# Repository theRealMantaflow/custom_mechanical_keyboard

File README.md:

# Custom STM32 Mechanical Keyboard

This repository contains the hardware design files (PCB schematics and mechanical enclosures) for a custom mechanical keyboard. The PCB is designed in **KiCad**, and the case/mechanical components are modeled in **FreeCAD**.

## Features

* **Microcontroller:** STM32F405RGT
* **Connectivity:** USB-C 2.0 with dedicated ESD protection (USBLC6-2SC6)
* **Switch Matrix:** 6x16 layout supporting up to 96 keys
* **Switches:** Cherry MX compatible, utilizing Khail hot-swap sockets
* **Anti-Ghosting:** Per-key diodes for full N-Key Rollover (NKRO)
* **Extras:** Support for a rotary encoder and broken-out SWD/I2C pins for easy debugging and expansion

## Repository Structure

* `/` - Contains the KiCad project, schematics, and PCB layout files.
* `/case/` - Contains the FreeCAD design files for the keyboard case and plate.
* `/pcbway_production/` - Contains the gerber files.

## Prerequisites & Environment Setup

Before opening the KiCad project files, you need to configure your KiCad environment with the appropriate custom libraries and plugins used in this design. 

### KiCad Package Installation

Follow these steps exactly to ensure all footprints and symbols load correctly:

1. **Add the ebastler repository:**
   * Open KiCad and go to the **Plugin and Content Manager**.
   * Click on **Manage Repositories** (usually at the bottom left).
   * Add a new repository with the following URL:
     [https://raw.githubusercontent.com/ebastler/KiCad-repository/main/repository.json](https://raw.githubusercontent.com/ebastler/KiCad-repository/main/repository.json)
2. **Install custom libraries:**
   * Switch the repository dropdown at the top of the Plugin Manager to the newly added `ebastler` repo.
   * Find and install the **`marbastlib`** package.
3. **Switch back to the official repository:**
   * Change the repository dropdown back to the official **KiCad** repository.
4. **Install required keyboard packages:**
   * Search for and install the **`Keyswitch KiCad Library`**.
   * *(Optional)* If you plan on modifying the PCB layout, install the **`Keyboard footprints placer`** plugin to make routing and placing switches easier.

Once these packages are installed, you can safely open the `.kicad_pro` file.

## Contributions

Feel free to fork this repository and submit pull requests if you have improvements for the PCB routing or case design. 

My Ko-fi link if you wanna support my efforts:  [Kofi](https://ko-fi.com/mantaflow)

## Thanks

Inspired from: [Modern Hobbyist](https://www.youtube.com/watch?v=u13yRbBiRYM)

## License
This project is licensed under the **GNU General Public License v3.0 (GPL-3.0)**. See the [LICENSE](LICENSE.txt) file for more details.

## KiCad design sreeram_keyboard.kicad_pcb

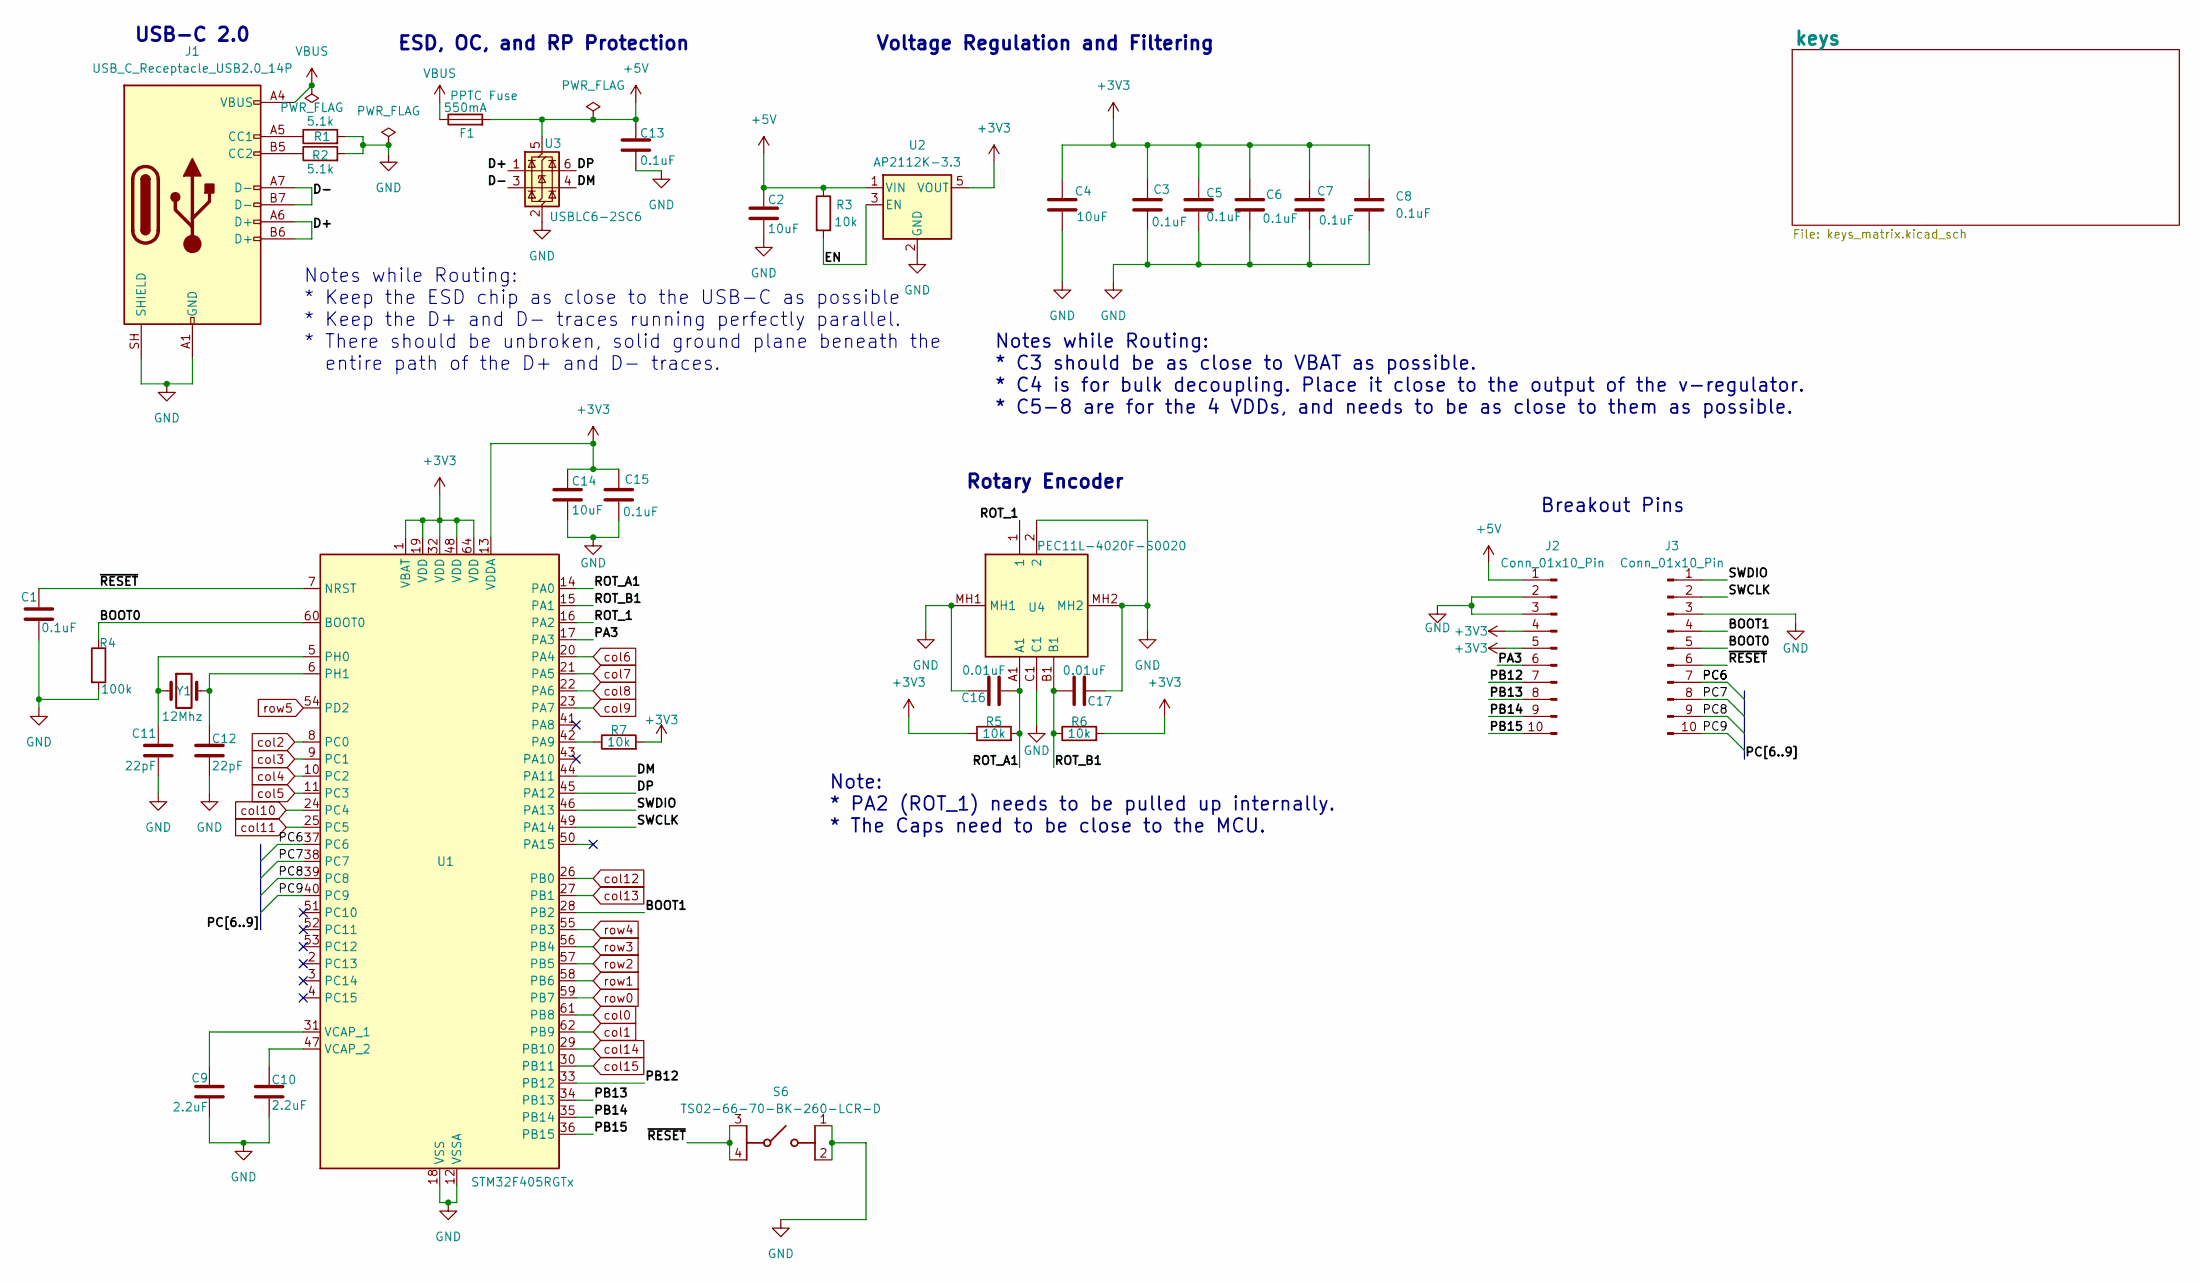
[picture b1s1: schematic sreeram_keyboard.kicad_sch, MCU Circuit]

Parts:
C1, C3, C5, C6, C7, C8, C13, C15: 0.1uF; C_0805_2012Metric_Pad1.18x1.45mm_HandSolder
C2, C4, C14: 10uF; C_0805_2012Metric_Pad1.18x1.45mm_HandSolder
C9, C10: 2.2uF; C_0805_2012Metric_Pad1.18x1.45mm_HandSolder
C11, C12: 22pF; C_0805_2012Metric_Pad1.18x1.45mm_HandSolder
C16, C17: 0.01uF; C_0805_2012Metric_Pad1.18x1.45mm_HandSolder
F1: 550mA; Fuse_1206_3216Metric_Pad1.42x1.75mm_HandSolder
J1: USB_C_Receptacle_USB2.0_14P; USB_C_Receptacle_GCT_USB4085
J2, J3: Conn_01x10_Pin; PinHeader_1x10_P2.54mm_Vertical
R1, R2: 5.1k; R_0805_2012Metric_Pad1.20x1.40mm_HandSolder
R3, R5, R6, R7: 10k; R_0805_2012Metric_Pad1.20x1.40mm_HandSolder
R4: 100k; R_0805_2012Metric_Pad1.20x1.40mm_HandSolder
S6: TS02-66-70-BK-260-LCR-D; TS0266100BK100LCRD; Mouser Part Number 179-TS026670BK260LCR
U1: STM32F405RGTx; LQFP-64_10x10mm_P0.5mm
U2: AP2112K-3.3; SOT95P285X140-5N
U3: USBLC6-2SC6; SOT-23-6
U4: PEC11L-4020F-S0020; PEC11L4120FS0020; Mouser Part Number 652-PEC11L4020FS0020
Y1: 12Mhz; ABLS

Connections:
+3V3: C3.1, C4.1, C5.1, C6.1, C7.1, C8.1, C14.1, C15.1, J2.4, J2.5, R5.1, R6.2, R7.2, U1.1 (VBAT), U1.13 (VDDA), U1.19 (VDD), U1.32 (VDD), U1.48 (VDD), U1.64 (VDD), U2.5 (VOUT)
+5V: C2.1, C13.1, F1.2, J2.1, R3.1, U2.1 (VIN), U3.5 (VBUS)
/BOOT0: J3.5, R4.1, U1.60 (BOOT0)
/BOOT1: J3.4, U1.28 (PB2)
/D+: J1.A6 (D+), J1.B6 (D+), U3.1 (I/O1)
/D-: J1.A7 (D-), J1.B7 (D-), U3.3 (I/O2)
/DM: U1.44 (PA11), U3.4 (I/O2)
/DP: U1.45 (PA12), U3.6 (I/O1)
/EN: R3.2, U2.3 (EN)
/PA3: J2.6, U1.17 (PA3)
/PB12: J2.7, U1.33 (PB12)
/PB13: J2.8, U1.34 (PB13)
/PB14: J2.9, U1.35 (PB14)
/PB15: J2.10, U1.36 (PB15)
/PC6: J3.7, U1.37 (PC6)
/PC7: J3.8, U1.38 (PC7)
/PC8: J3.9, U1.39 (PC8)
/PC9: J3.10, U1.40 (PC9)
/ROT_1: U1.16 (PA2), U4.1
/ROT_A1: C16.2, R5.2, U1.14 (PA0), U4.A1
/ROT_B1: C17.1, R6.1, U1.15 (PA1), U4.B1
/SWCLK: J3.2, U1.49 (PA14)
/SWDIO: J3.1, U1.46 (PA13)
/~RESET: C1.1, J3.6, S6.3 (COM_1), S6.4 (COM_2), U1.7 (NRST)
GND: C1.2, C2.2, C3.2, C4.2, C5.2, C6.2, C7.2, C8.2, C9.2, C10.2, C11.2, C12.2, C13.2, C14.2, C15.2, C16.1, C17.2, J1.A1 (GND), J1.A12 (GND), J1.B1 (GND), J1.B12 (GND), J1.SH (SHIELD), J2.2, J2.3, J3.3, R1.2, R2.2, R4.2, S6.1 (NO_1), S6.2 (NO_2), U1.12 (VSSA), U1.18 (VSS), U1.63 (VSS), U2.2 (GND), U3.2 (GND), U4.2, U4.C1, U4.MH1, U4.MH2
unnamed: J1.A5 (CC1), R1.1
unnamed: J1.B5 (CC2), R2.1
unnamed: R7.1, U1.42 (PA9)
unnamed: C11.1, U1.5 (PH0), Y1.1
unnamed: C12.1, U1.6 (PH1), Y1.2
unnamed: C9.1, U1.31 (VCAP_1)
unnamed: C10.1, U1.47 (VCAP_2)
VBUS: F1.1, J1.A4 (VBUS), J1.A9 (VBUS), J1.B4 (VBUS), J1.B9 (VBUS)
col0: U1.61 (PB8); also elsewhere on the board
col1: U1.62 (PB9); also elsewhere on the board
col2: U1.8 (PC0); also elsewhere on the board
col3: U1.9 (PC1); also elsewhere on the board
col4: U1.10 (PC2); also elsewhere on the board
col5: U1.11 (PC3); also elsewhere on the board
col6: U1.20 (PA4); also elsewhere on the board
col7: U1.21 (PA5); also elsewhere on the board
col8: U1.22 (PA6); also elsewhere on the board
col9: U1.23 (PA7); also elsewhere on the board
col10: U1.24 (PC4); also elsewhere on the board
col11: U1.25 (PC5); also elsewhere on the board
col12: U1.26 (PB0); also elsewhere on the board
col13: U1.27 (PB1); also elsewhere on the board
col14: U1.29 (PB10); also elsewhere on the board
col15: U1.30 (PB11); also elsewhere on the board
row0: U1.59 (PB7); also elsewhere on the board
row1: U1.58 (PB6); also elsewhere on the board
row2: U1.57 (PB5); also elsewhere on the board
row3: U1.56 (PB4); also elsewhere on the board
row4: U1.55 (PB3); also elsewhere on the board
row5: U1.54 (PD2); also elsewhere on the board

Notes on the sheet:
Notes while Routing: * C3 should be as close to VBAT as possible. * C4 is for bulk decoupling. Place it close to the output of the v-regulator. * C5-8 are for the 4 VDDs, and needs to be as close to them as possible.
Notes while Routing: * Keep the ESD chip as close to the USB-C as possible * Keep the D+ and D- traces running perfectly parallel. * There should be unbroken, solid ground plane beneath the entire path of the D+ and D- traces.
USB-C 2.0
Voltage Regulation and Filtering
ESD, OC, and RP Protection
Note: * PA2 (ROT_1) needs to be pulled up internally. * The Caps need to be close to the MCU.
Rotary Encoder
Breakout Pins

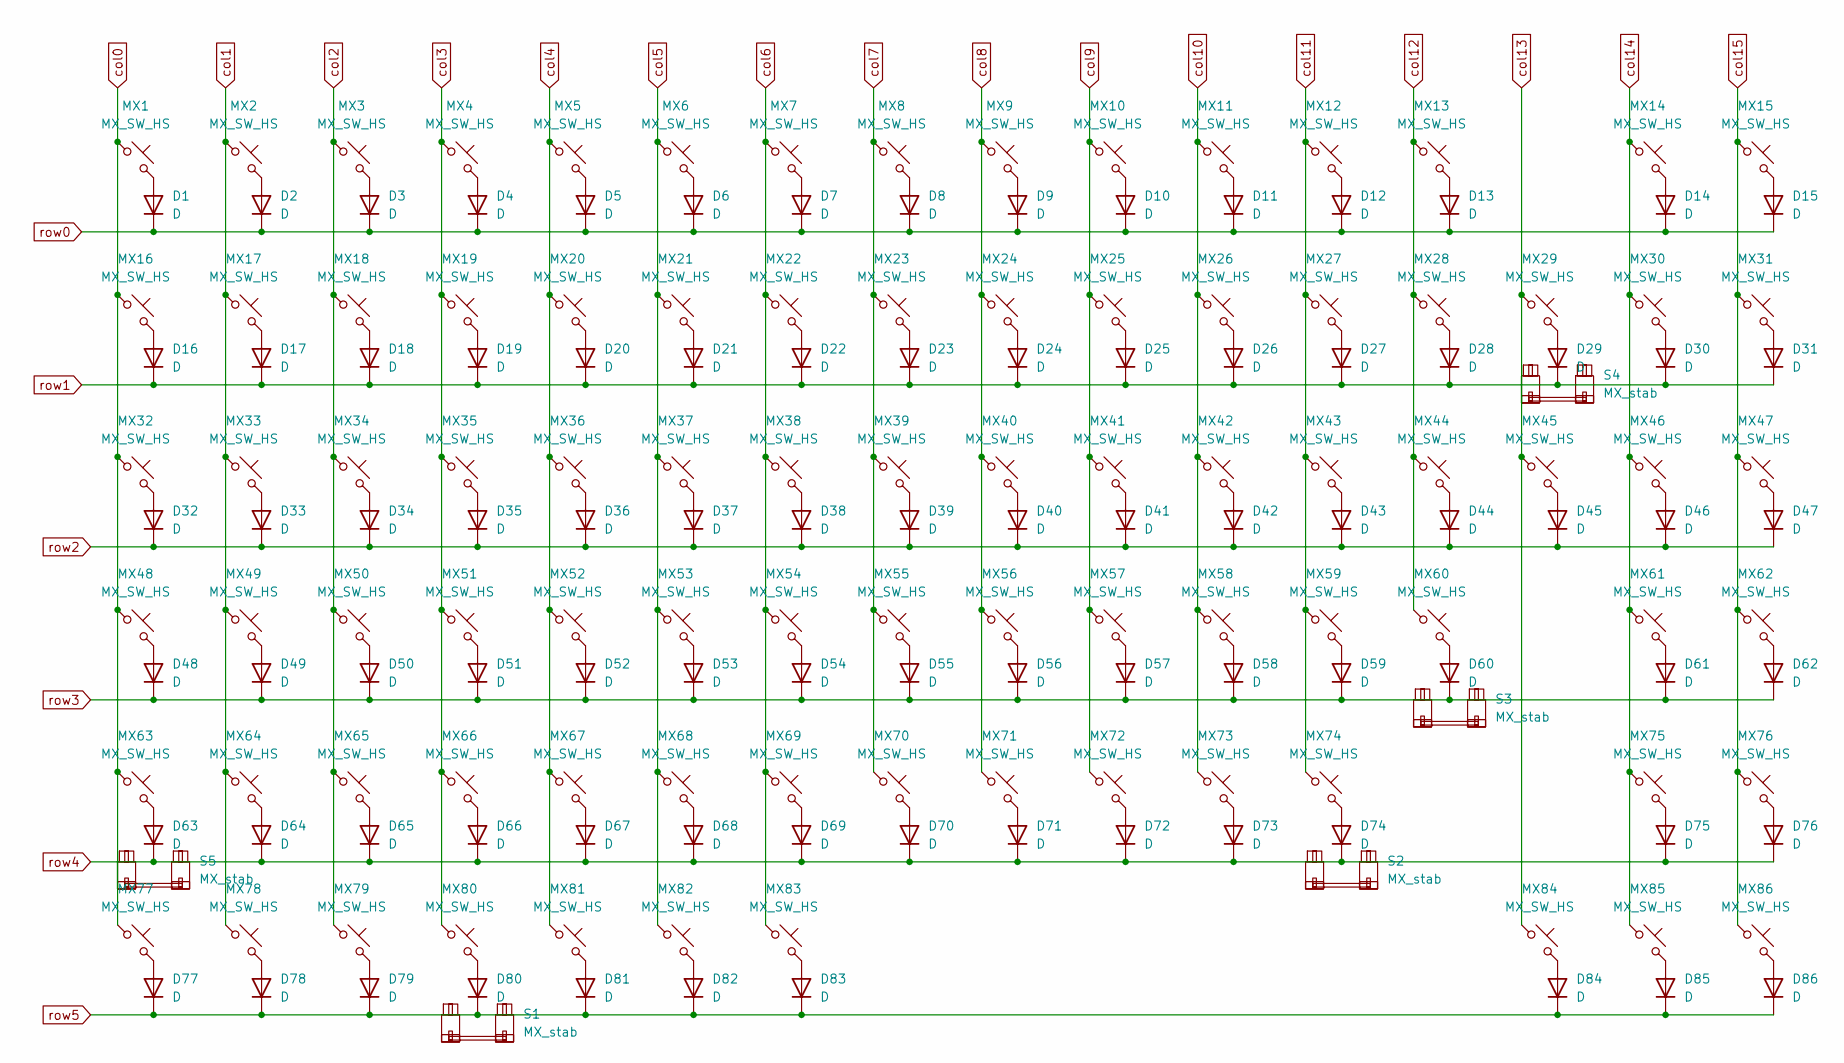
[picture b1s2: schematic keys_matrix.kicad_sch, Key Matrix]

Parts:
D1, D2, D3, D4, D5, D6, D7, D8, D9, D10, D11, D12, D13, D14, D15, D16, D17, D18, D19, D20, D21, D22, D23, D24, D25, D26, D27, D28, D29, D30, D31, D32, D33, D34, D35, D36, D37, D38, D39, D40, D41, D42, D43, D44, D45, D46, D47, D48, D49, D50, D51, D52, D53, D54, D55, D56, D57, D58, D59, D60, D61, D62, D63, D64, D65, D66, D67, D68, D69, D70, D71, D72, D73, D74, D75, D76, D77, D78, D79, D80, D81, D82, D83, D84, D85, D86: D; D_SOD-123
MX1, MX2, MX3, MX4, MX5, MX6, MX7, MX8, MX9, MX10, MX11, MX12, MX13, MX14, MX15, MX16, MX17, MX18, MX19, MX20, MX21, MX22, MX23, MX24, MX25, MX26, MX27, MX28, MX29, MX30, MX31, MX32, MX33, MX34, MX35, MX36, MX37, MX38, MX39, MX40, MX41, MX42, MX43, MX44, MX45, MX46, MX47, MX48, MX49, MX50, MX51, MX52, MX53, MX54, MX55, MX56, MX57, MX58, MX59, MX60, MX61, MX62, MX63, MX64, MX65, MX66, MX67, MX68, MX69, MX70, MX71, MX72, MX73, MX74, MX75, MX76, MX77, MX78, MX79, MX80, MX81, MX82, MX83, MX84, MX85, MX86: MX_SW_HS; SW_MX_HS_S_CPG151101S11_1u
S1: MX_stab; STAB_MX_P_6.25u
S2, S3, S4, S5: MX_stab; STAB_MX_P_2u

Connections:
unnamed: D1.2 (A), MX1.2
unnamed: D2.2 (A), MX2.2
unnamed: D3.2 (A), MX3.2
unnamed: D4.2 (A), MX4.2
unnamed: D5.2 (A), MX5.2
unnamed: D6.2 (A), MX6.2
unnamed: D7.2 (A), MX7.2
unnamed: D8.2 (A), MX8.2
unnamed: D9.2 (A), MX9.2
unnamed: D10.2 (A), MX10.2
unnamed: D11.2 (A), MX11.2
unnamed: D12.2 (A), MX12.2
unnamed: D13.2 (A), MX13.2
unnamed: D14.2 (A), MX14.2
unnamed: D15.2 (A), MX15.2
unnamed: D16.2 (A), MX16.2
unnamed: D17.2 (A), MX17.2
unnamed: D18.2 (A), MX18.2
unnamed: D19.2 (A), MX19.2
unnamed: D20.2 (A), MX20.2
unnamed: D21.2 (A), MX21.2
unnamed: D22.2 (A), MX22.2
unnamed: D23.2 (A), MX23.2
unnamed: D24.2 (A), MX24.2
unnamed: D25.2 (A), MX25.2
unnamed: D26.2 (A), MX26.2
unnamed: D27.2 (A), MX27.2
unnamed: D28.2 (A), MX28.2
unnamed: D29.2 (A), MX29.2
unnamed: D30.2 (A), MX30.2
unnamed: D31.2 (A), MX31.2
unnamed: D32.2 (A), MX32.2
unnamed: D33.2 (A), MX33.2
unnamed: D34.2 (A), MX34.2
unnamed: D35.2 (A), MX35.2
unnamed: D36.2 (A), MX36.2
unnamed: D37.2 (A), MX37.2
unnamed: D38.2 (A), MX38.2
unnamed: D39.2 (A), MX39.2
unnamed: D40.2 (A), MX40.2
unnamed: D41.2 (A), MX41.2
unnamed: D42.2 (A), MX42.2
unnamed: D43.2 (A), MX43.2
unnamed: D44.2 (A), MX44.2
unnamed: D45.2 (A), MX45.2
unnamed: D46.2 (A), MX46.2
unnamed: D47.2 (A), MX47.2
unnamed: D48.2 (A), MX48.2
unnamed: D49.2 (A), MX49.2
unnamed: D50.2 (A), MX50.2
unnamed: D51.2 (A), MX51.2
unnamed: D52.2 (A), MX52.2
unnamed: D53.2 (A), MX53.2
unnamed: D54.2 (A), MX54.2
unnamed: D55.2 (A), MX55.2
unnamed: D56.2 (A), MX56.2
unnamed: D57.2 (A), MX57.2
unnamed: D58.2 (A), MX58.2
unnamed: D59.2 (A), MX59.2
unnamed: D60.2 (A), MX60.2
unnamed: D61.2 (A), MX61.2
unnamed: D62.2 (A), MX62.2
unnamed: D63.2 (A), MX63.2
unnamed: D64.2 (A), MX64.2
unnamed: D65.2 (A), MX65.2
unnamed: D66.2 (A), MX66.2
unnamed: D67.2 (A), MX67.2
unnamed: D68.2 (A), MX68.2
unnamed: D69.2 (A), MX69.2
unnamed: D70.2 (A), MX70.2
unnamed: D71.2 (A), MX71.2
unnamed: D72.2 (A), MX72.2
unnamed: D73.2 (A), MX73.2
unnamed: D74.2 (A), MX74.2
unnamed: D75.2 (A), MX75.2
unnamed: D76.2 (A), MX76.2
unnamed: D77.2 (A), MX77.2
unnamed: D78.2 (A), MX78.2
unnamed: D79.2 (A), MX79.2
unnamed: D80.2 (A), MX80.2
unnamed: D81.2 (A), MX81.2
unnamed: D82.2 (A), MX82.2
unnamed: D83.2 (A), MX83.2
unnamed: D84.2 (A), MX84.2
unnamed: D85.2 (A), MX85.2
unnamed: D86.2 (A), MX86.2
col0: MX1.1, MX16.1, MX32.1, MX48.1, MX63.1, MX77.1; also elsewhere on the board
col1: MX2.1, MX17.1, MX33.1, MX49.1, MX64.1, MX78.1; also elsewhere on the board
col2: MX3.1, MX18.1, MX34.1, MX50.1, MX65.1, MX79.1; also elsewhere on the board
col3: MX4.1, MX19.1, MX35.1, MX51.1, MX66.1, MX80.1; also elsewhere on the board
col4: MX5.1, MX20.1, MX36.1, MX52.1, MX67.1, MX81.1; also elsewhere on the board
col5: MX6.1, MX21.1, MX37.1, MX53.1, MX68.1, MX82.1; also elsewhere on the board
col6: MX7.1, MX22.1, MX38.1, MX54.1, MX69.1, MX83.1; also elsewhere on the board
col7: MX8.1, MX23.1, MX39.1, MX55.1, MX70.1; also elsewhere on the board
col8: MX9.1, MX24.1, MX40.1, MX56.1, MX71.1; also elsewhere on the board
col9: MX10.1, MX25.1, MX41.1, MX57.1, MX72.1; also elsewhere on the board
col10: MX11.1, MX26.1, MX42.1, MX58.1, MX73.1; also elsewhere on the board
col11: MX12.1, MX27.1, MX43.1, MX59.1, MX74.1; also elsewhere on the board
col12: MX13.1, MX28.1, MX44.1, MX60.1; also elsewhere on the board
col13: MX29.1, MX45.1, MX84.1; also elsewhere on the board
col14: MX14.1, MX30.1, MX46.1, MX61.1, MX75.1, MX85.1; also elsewhere on the board
col15: MX15.1, MX31.1, MX47.1, MX62.1, MX76.1, MX86.1; also elsewhere on the board
row0: D1.1 (K), D2.1 (K), D3.1 (K), D4.1 (K), D5.1 (K), D6.1 (K), D7.1 (K), D8.1 (K), D9.1 (K), D10.1 (K), D11.1 (K), D12.1 (K), D13.1 (K), D14.1 (K), D15.1 (K); also elsewhere on the board
row1: D16.1 (K), D17.1 (K), D18.1 (K), D19.1 (K), D20.1 (K), D21.1 (K), D22.1 (K), D23.1 (K), D24.1 (K), D25.1 (K), D26.1 (K), D27.1 (K), D28.1 (K), D29.1 (K), D30.1 (K), D31.1 (K); also elsewhere on the board
row2: D32.1 (K), D33.1 (K), D34.1 (K), D35.1 (K), D36.1 (K), D37.1 (K), D38.1 (K), D39.1 (K), D40.1 (K), D41.1 (K), D42.1 (K), D43.1 (K), D44.1 (K), D45.1 (K), D46.1 (K), D47.1 (K); also elsewhere on the board
row3: D48.1 (K), D49.1 (K), D50.1 (K), D51.1 (K), D52.1 (K), D53.1 (K), D54.1 (K), D55.1 (K), D56.1 (K), D57.1 (K), D58.1 (K), D59.1 (K), D60.1 (K), D61.1 (K), D62.1 (K); also elsewhere on the board
row4: D63.1 (K), D64.1 (K), D65.1 (K), D66.1 (K), D67.1 (K), D68.1 (K), D69.1 (K), D70.1 (K), D71.1 (K), D72.1 (K), D73.1 (K), D74.1 (K), D75.1 (K), D76.1 (K); also elsewhere on the board
row5: D77.1 (K), D78.1 (K), D79.1 (K), D80.1 (K), D81.1 (K), D82.1 (K), D83.1 (K), D84.1 (K), D85.1 (K), D86.1 (K); also elsewhere on the board

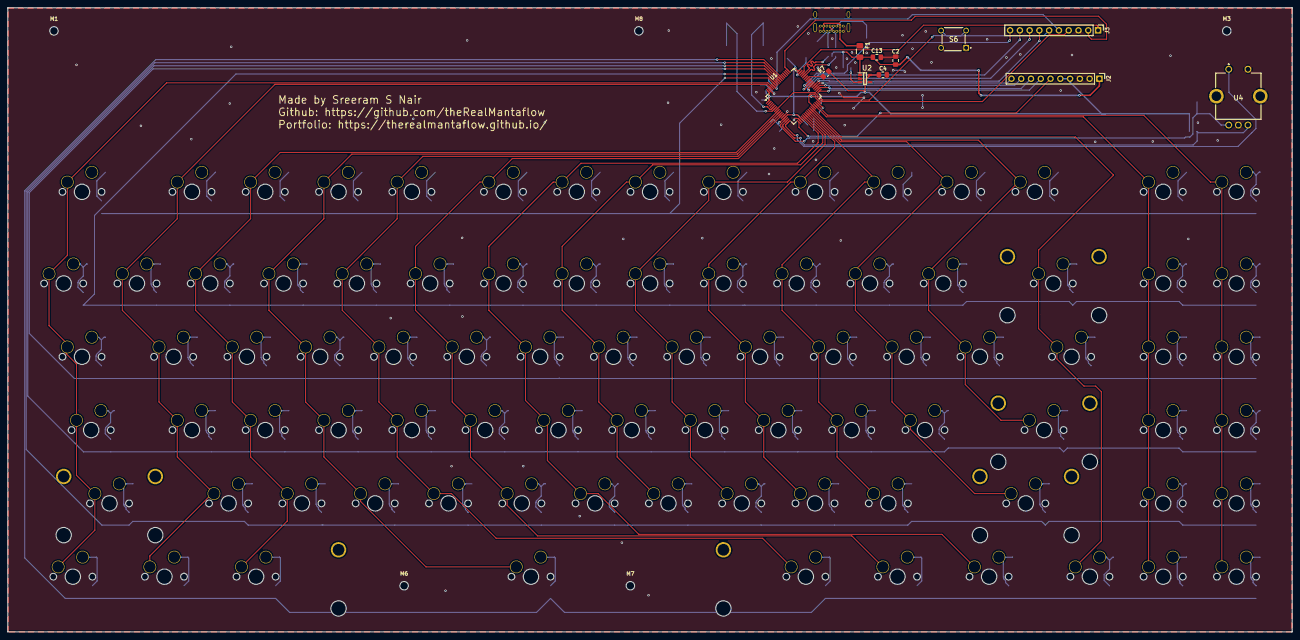
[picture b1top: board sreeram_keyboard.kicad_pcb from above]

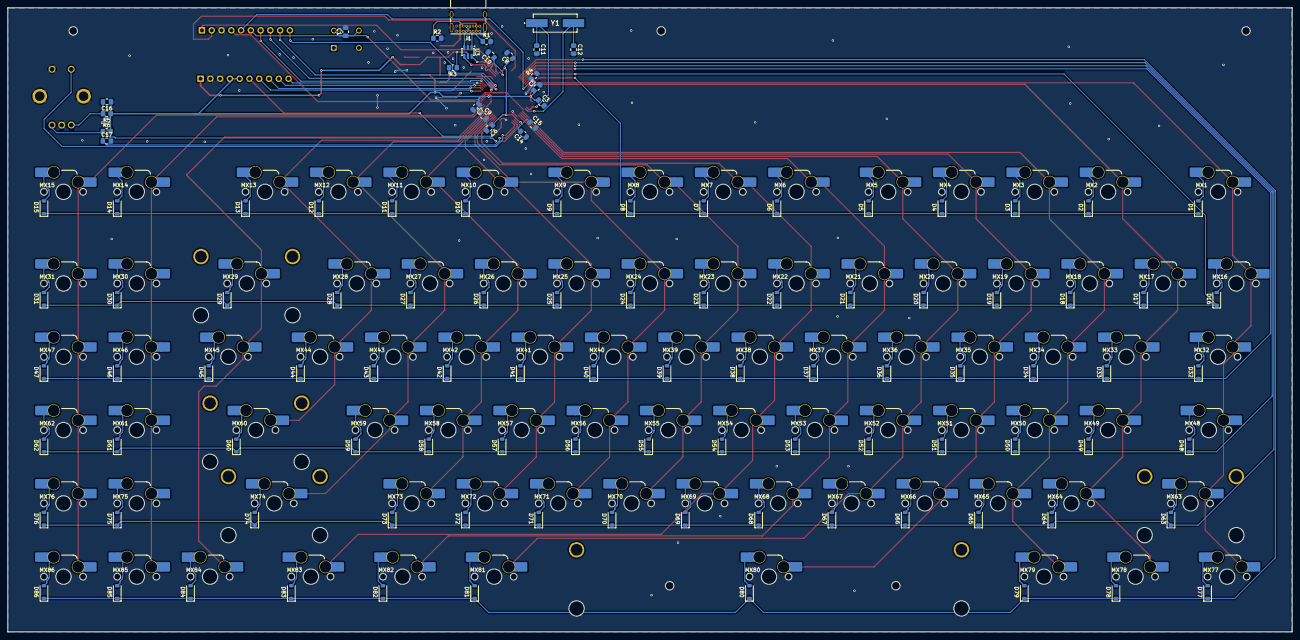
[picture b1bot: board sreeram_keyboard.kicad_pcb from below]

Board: 2 copper layers, 333.8 x 162.2 mm, 216 parts (195 on the bottom side), 141 nets.

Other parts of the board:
M1, M3, M6, M7, M8: MountingHole_2.2mm_M2

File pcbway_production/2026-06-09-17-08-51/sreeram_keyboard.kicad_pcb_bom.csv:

Designator,Quantity,Value,Footprint,Package,MPN,DNP,Mount_Type,KiLib_Generator
"C1, C13, C15, C3, C5, C6, C7, C8",8,0.1uF,C_0805_2012Metric_Pad1.18x1.45mm_HandSolder,,,,smt,SMD_2terminal_chip_molded
"C10, C9",2,2.2uF,C_0805_2012Metric_Pad1.18x1.45mm_HandSolder,,,,smt,SMD_2terminal_chip_molded
"C11, C12",2,22pF,C_0805_2012Metric_Pad1.18x1.45mm_HandSolder,,,,smt,SMD_2terminal_chip_molded
"C14, C2, C4",3,10uF,C_0805_2012Metric_Pad1.18x1.45mm_HandSolder,,,,smt,SMD_2terminal_chip_molded
"C16, C17",2,0.01uF,C_0805_2012Metric_Pad1.18x1.45mm_HandSolder,,,,smt,SMD_2terminal_chip_molded
"D1, D10, D11, D12, D13, D14, D15, D16, D17, D18, D19, D2, D20, D21, D22, D23, D24, D25, D26, D27, D28, D29, D3, D30, D31, D32, D33, D34, D35, D36, D37, D38, D39, D4, D40, D41, D42, D43, D44, D45, D46, D47, D48, D49, D5, D50, D51, D52, D53, D54, D55, D56, D57, D58, D59, D6, D60, D61, D62, D63, D64, D65, D66, D67, D68, D69, D7, D70, D71, D72, D73, D74, D75, D76, D77, D78, D79, D8, D80, D81, D82, D83, D84, D85, D86, D9",86,D,D_SOD-123,,,,smt,
F1,1,550mA,Fuse_1206_3216Metric_Pad1.42x1.75mm_HandSolder,,,,smt,SMD_2terminal_chip_molded
J1,1,USB_C_Receptacle_USB2.0_14P,USB_C_Receptacle_GCT_USB4085,,,,tht,
"J2, J3",2,Conn_01x10_Pin,PinHeader_1x10_P2.54mm_Vertical,,,,tht,connector/pin_header_socket
"MX1, MX10, MX11, MX12, MX13, MX14, MX15, MX16, MX17, MX18, MX19, MX2, MX20, MX21, MX22, MX23, MX24, MX25, MX26, MX27, MX28, MX29, MX3, MX30, MX31, MX32, MX33, MX34, MX35, MX36, MX37, MX38, MX39, MX4, MX40, MX41, MX42, MX43, MX44, MX45, MX46, MX47, MX48, MX49, MX5, MX50, MX51, MX52, MX53, MX54, MX55, MX56, MX57, MX58, MX59, MX6, MX60, MX61, MX62, MX63, MX64, MX65, MX66, MX67, MX68, MX69, MX7, MX70, MX71, MX72, MX73, MX74, MX75, MX76, MX77, MX78, MX79, MX8, MX80, MX81, MX82, MX83, MX84, MX85, MX86, MX9",86,MX_SW_HS,SW_MX_HS_S_CPG151101S11_1u,,,,smt,
"R1, R2",2,5.1k,R_0805_2012Metric_Pad1.20x1.40mm_HandSolder,,,,smt,SMD_2terminal_chip_molded
"R3, R5, R6, R7",4,10k,R_0805_2012Metric_Pad1.20x1.40mm_HandSolder,,,,smt,SMD_2terminal_chip_molded
R4,1,100k,R_0805_2012Metric_Pad1.20x1.40mm_HandSolder,,,,smt,SMD_2terminal_chip_molded
S6,1,TS02-66-70-BK-260-LCR-D,TS0266100BK100LCRD,,,,tht,
U1,1,STM32F405RGTx,LQFP-64_10x10mm_P0.5mm,,,,smt,package/gullwing
U2,1,AP2112K-3.3,SOT95P285X140-5N,,,,smt,
U3,1,USBLC6-2SC6,SOT-23-6,,,,smt,package/gullwing
U4,1,PEC11L-4020F-S0020,PEC11L4120FS0020,,,,tht,
Y1,1,12Mhz,ABLS,,,,smt,

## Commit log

2026-06-12 Create FUNDING.yml
    added kofi
2026-06-12 Add files via upload
    Uploaded the files
2026-06-13 kofi-logo
2026-06-13 Added GPLv3 licence
2026-06-13 Readme Added
2026-06-13 Minor modification
